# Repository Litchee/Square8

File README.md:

8 SQUARE - Heartbeat Necklace Soldering Kit
-------------

8 SQUARE is a lovely and eye catching necklace that shows off your geek attitude. We designed it to help you build up your confidence as a hardware maker. With the soldering iron held in your hand, and detailed tutorial aside, you can make a red heart bounce on the 8x8 LED matrix. 

**Easy to Solder**

8 SQUARE is friendly when it comes to soldering. Components chosen to fulfill the function are all easiest to solder and appropriate distance between each two pads is kept to ensure people without any soldering experience can get it run with only a little effort.

**Arduino Compatible Microcontroller**

8 SQUARE features a classic Atmega328 as its processor. You can totally reprogram it as a Arduino UNO - the most widely adapted Arduino board for now. Thousands of tutorials and libraries over the community are easily to found when you need help to support your next Arduino project with 8 SQUARE.

**Friendly to Sewing**

7 signal pins and 4 power pins are routed our as much larger circular pads along 8 SQUARE. They are designed for further exploration with fabric. The through hole of these signals are large enough to let you put through any regular needles and tie a knot to confirm the connection.  

<br>
**Part List**

- Base board x 1
- 1k ohm resistor x 4
- 2k ohm resistor x 1
- 10k ohm resistor x 1
- 100nF capacitor x 4
- 3mm red LED x 1
- 3mm green LED x 1
- Push button x 1
- Switch x 1
- Coin battery holder x 1
- LIR2032 coin battery x 1
- 8 pin female header x 2
- 8x8 LED matrix x 1
- leather rope x 1
- ring x 1
- tutorial x 1

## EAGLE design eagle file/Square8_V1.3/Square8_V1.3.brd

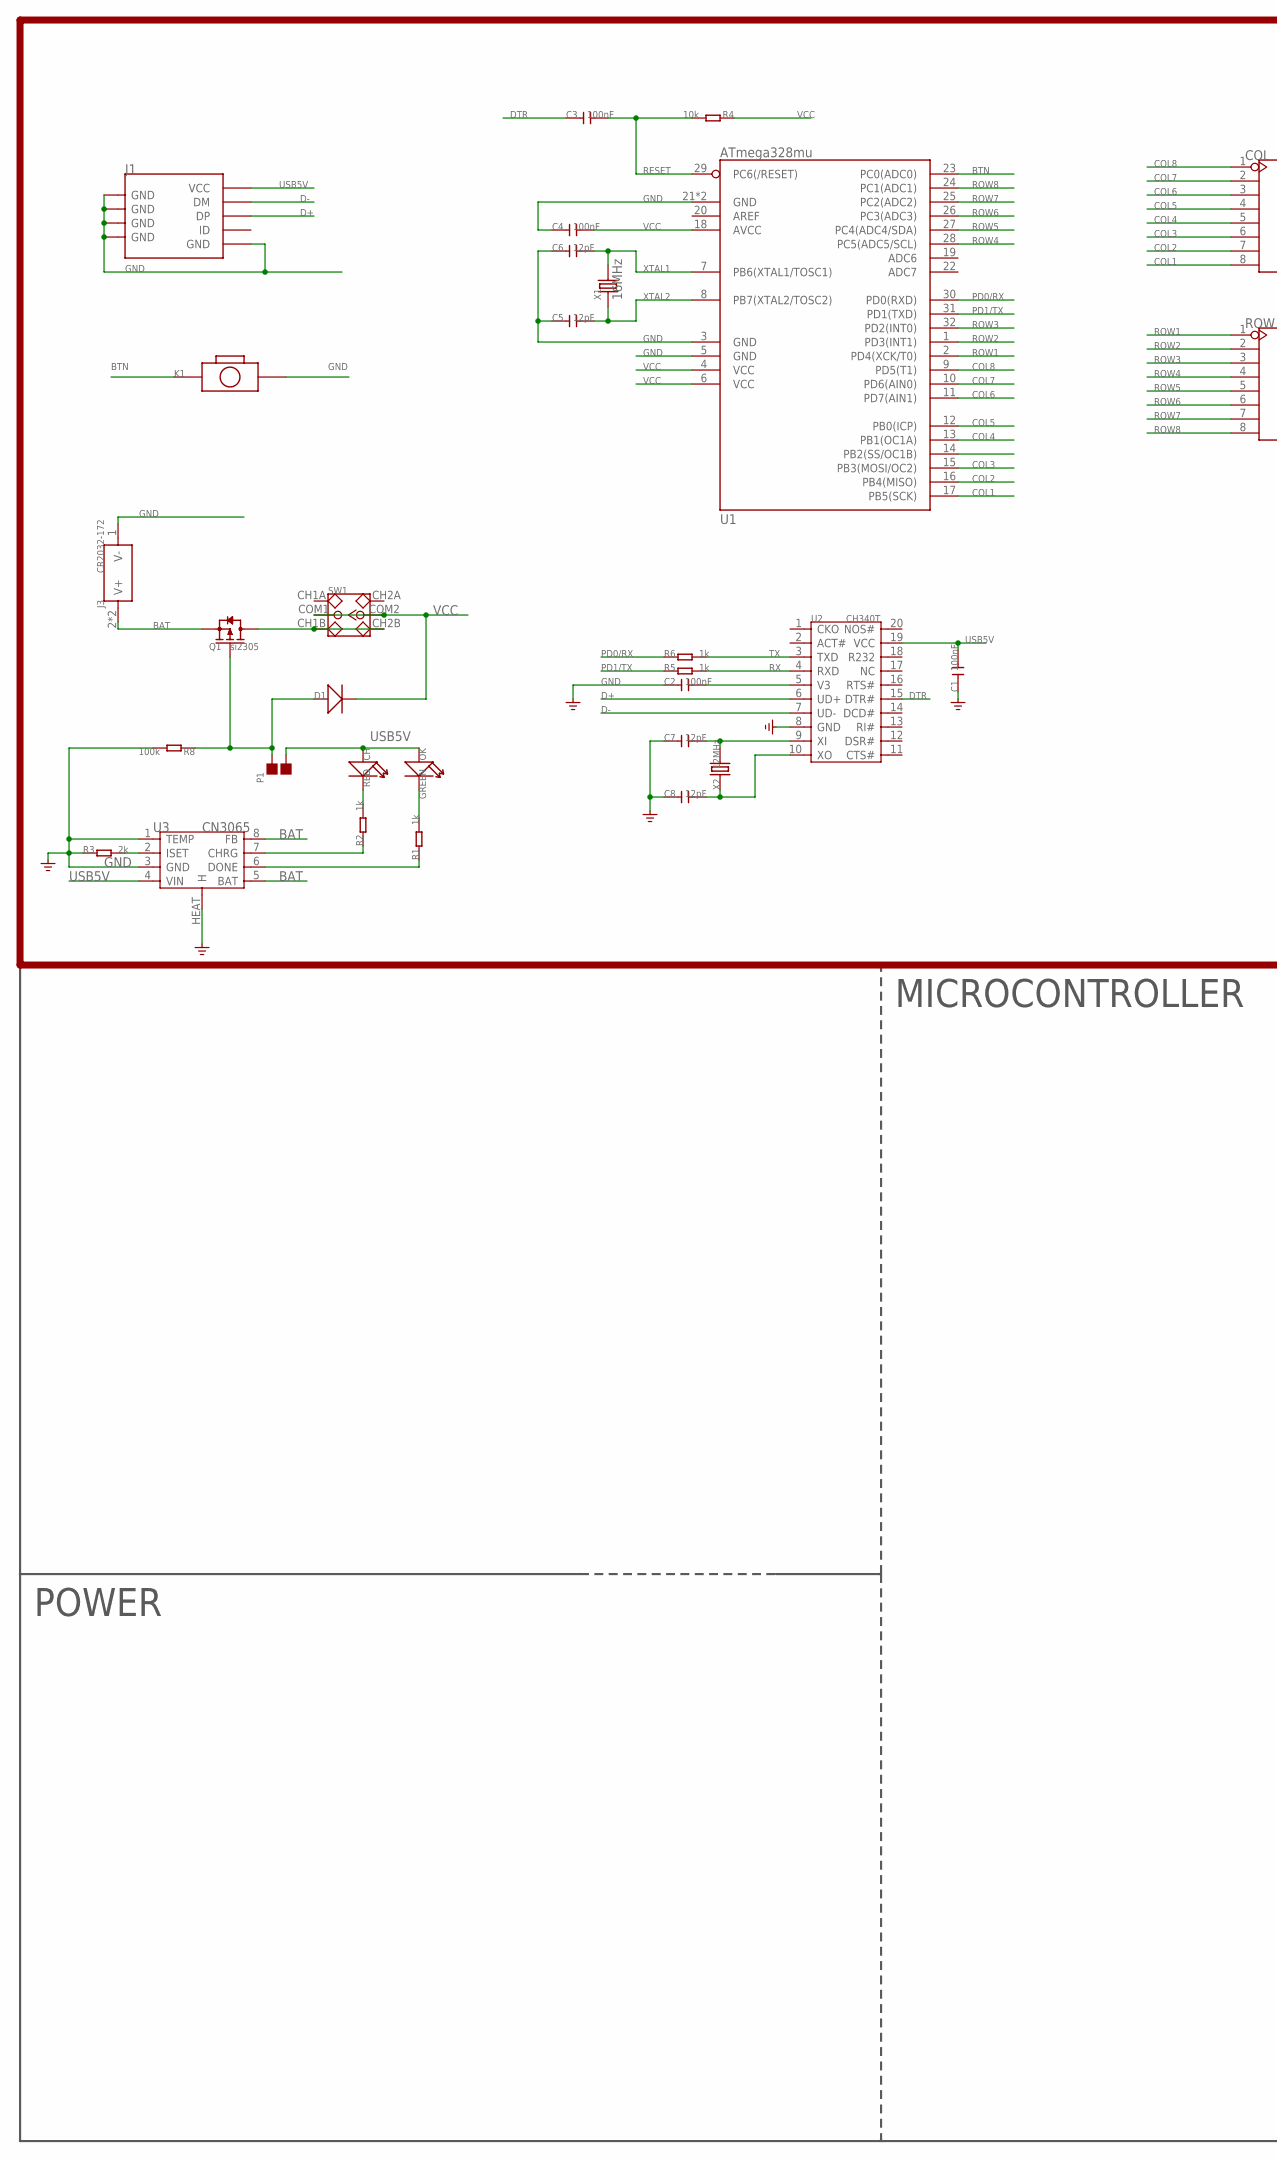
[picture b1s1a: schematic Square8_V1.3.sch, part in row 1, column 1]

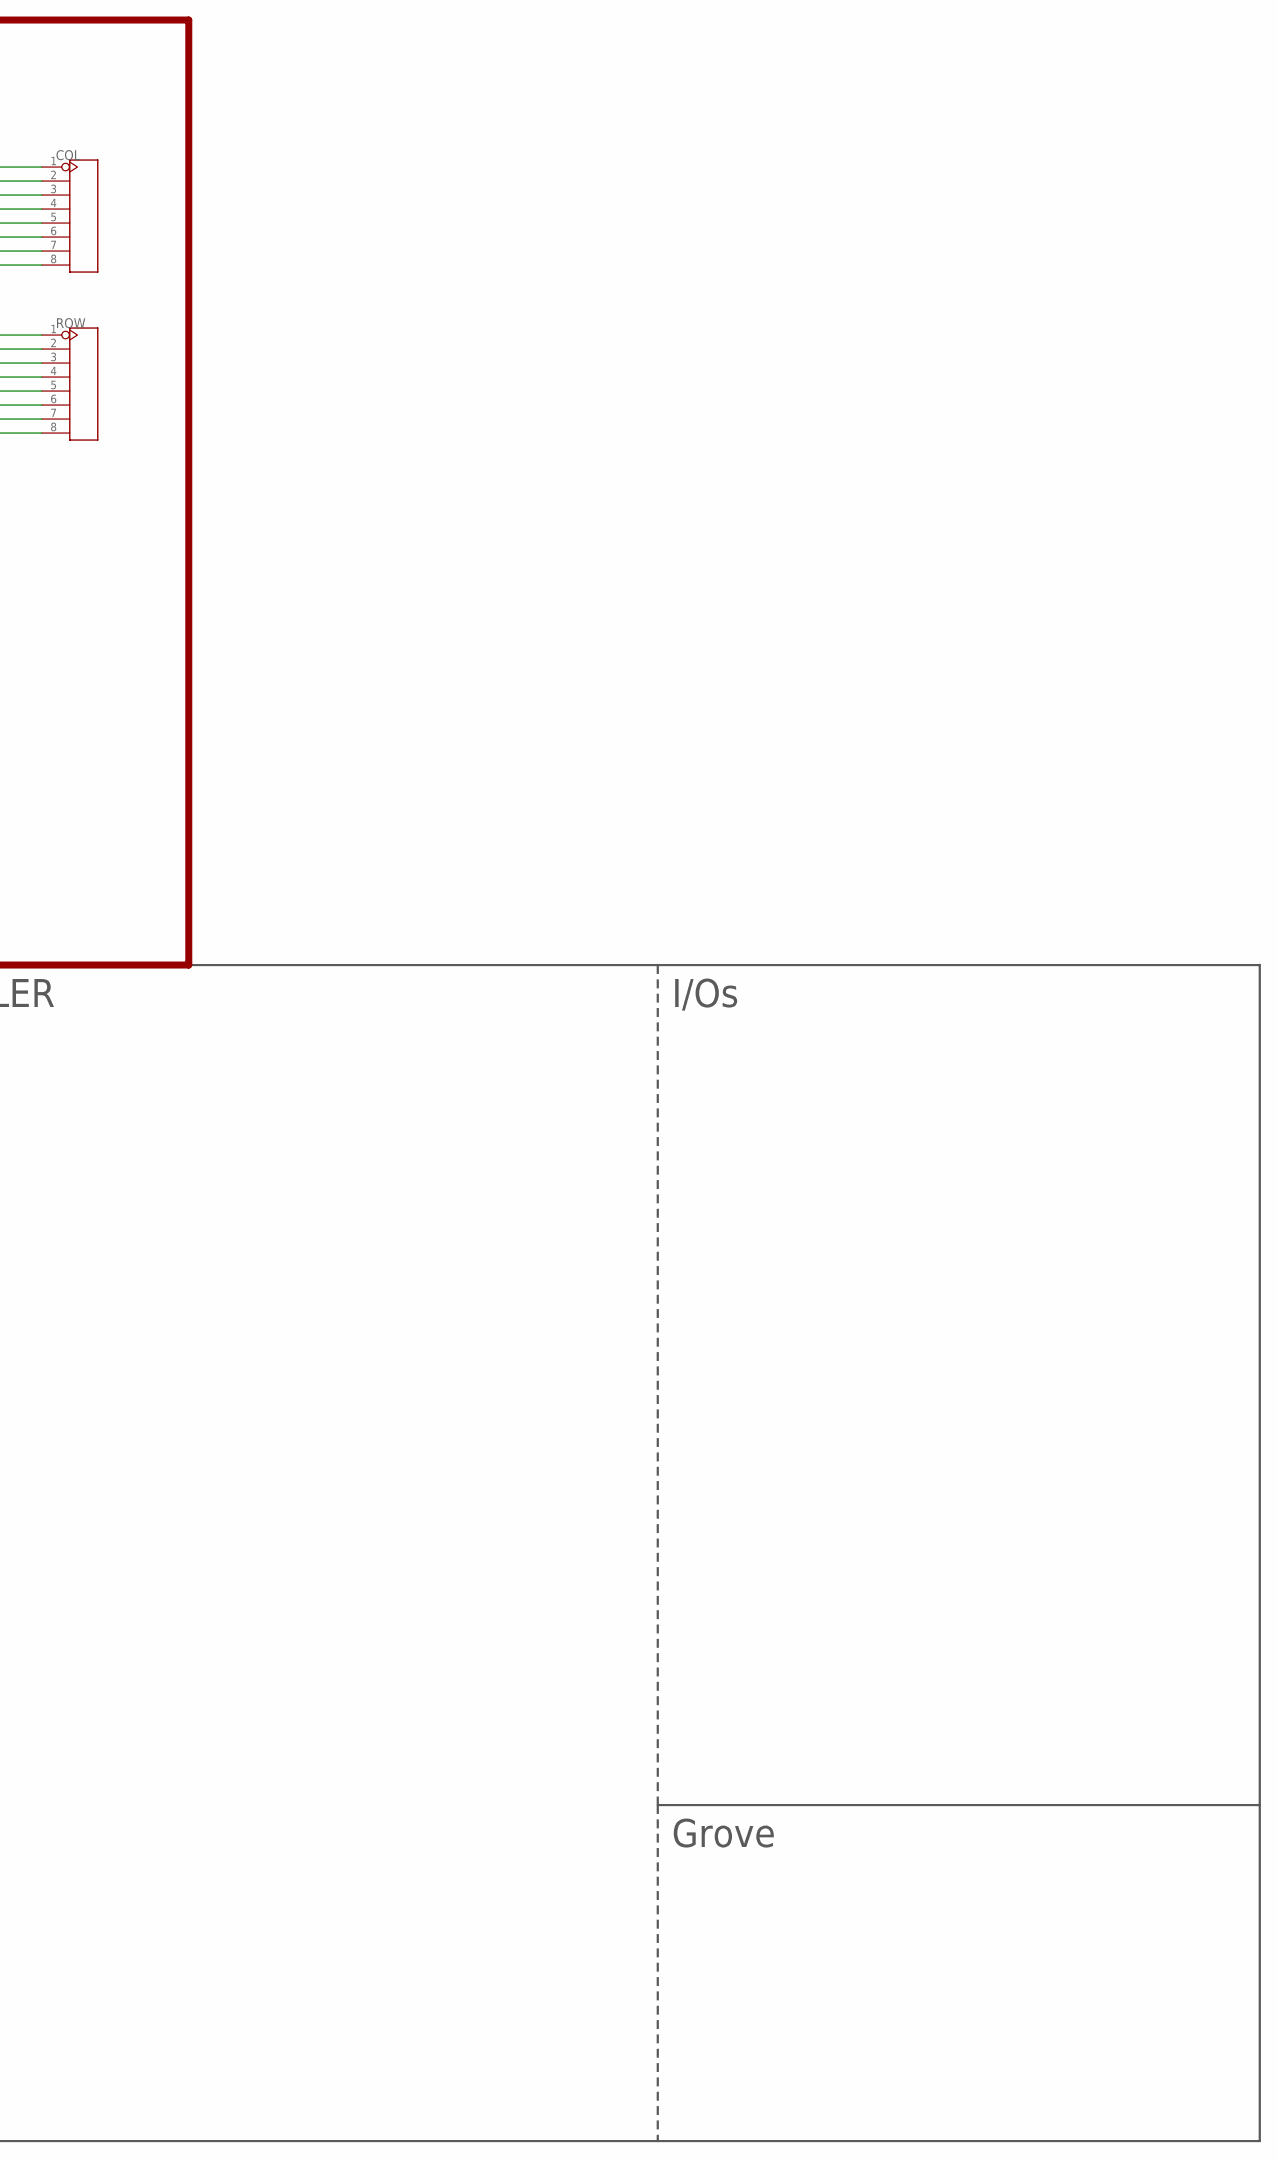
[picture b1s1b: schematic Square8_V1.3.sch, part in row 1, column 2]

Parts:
C1, C2, C3, C4: 100nF; CERAMIC-2.54
C5, C6, C7, C8: 12pF; C0603
CH: RED; LED-2P-2.54-3MM
COL: HEADER-8P-2.54; 8P-2.54
D1: D'B130L-13-F'; SMA
J1: USB-MINIUSB-5P-MICRO; MICRO-USB
J3: CR2032-172; 2032-D20-CIRCLE
K1: BUTTON-2P'TS-1101F'; 2P-3.4X6.0X3.55H-90D
OK: GREEN; LED-2P-2.54-3MM
P1: PAD-JUMPER-2P; 2P-SMD-1.78X1.27
Q1: si2305; SOT23
R1, R2, R5, R6: 1k; R0204/7
R3: 2k; R0204/7
R4: 10k; R0204/7
R8: 100k; R0603
ROW: HEADER-8P-2.54; 8P-2.54
SW1: SWITCH-2CH-6P'90D'; 6P-2CH-2.5-9.1X3.5X3.2H-90D
U1: ATmega328mu; MLF32X-W/HEAT
U2: CH340T; SSOP20
U3: CN3065; DFN8
X1: 16MHz; HC49S
X2: 12MHz; HC49S

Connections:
BAT: J3.2 (V+), J3.3 (V+), Q1.2 (S), U3.5 (BAT), U3.8 (FB)
BTN: K1.P$1 (1), U1.23 (PC0(ADC0))
CH_STATE: R1.1, U3.6 (DONE)
COL1: COL.8, U1.17 (PB5(SCK))
COL2: COL.7, U1.16 (PB4(MISO))
COL3: COL.6, U1.15 (PB3(MOSI/OC2))
COL4: COL.5, U1.13 (PB1(OC1A))
COL5: COL.4, U1.12 (PB0(ICP))
COL6: COL.3, U1.11 (PD7(AIN1))
COL7: COL.2, U1.10 (PD6(AIN0))
COL8: COL.1, U1.9 (PD5(T1))
D+: J1.3 (DP), U2.6 (UD+)
D-: J1.2 (DM), U2.7 (UD-)
DTR: C3.1, U2.15 (DTR#)
GND: C1.1, C2.1, C4.1, C5.1, C6.1, C7.1, C8.1, J1.5 (GND), J1.S1 (GND), J1.S2 (GND), J1.S3 (GND), J1.S4 (GND), J1.S5 (GND), J1.S6 (GND), J3.1 (V-), K1.P$2 (2), R3.1, R8.2, U1.3 (GND), U1.5 (GND), U1.21 (GND), U1.HEAT (GND), U2.8 (GND), U3.1 (TEMP), U3.3 (GND), U3.HEAT (H)
unnamed: R2.1, U3.7 (CHRG)
unnamed: OK.K (-), R1.2
unnamed: D1.2 (+), P1.2, Q1.1 (G), R8.1
unnamed: CH.K (-), R2.2
unnamed: R3.2, U3.2 (ISET)
unnamed: C7.2, U2.9 (XI), X2.2
unnamed: C8.2, U2.10 (XO), X2.1
unnamed: Q1.3 (D), SW1.CH1B, SW1.CH2B
PD0/RX: R6.1, U1.30 (PD0(RXD))
PD1/TX: R5.1, U1.31 (PD1(TXD))
RESET: C3.2, R4.2, U1.29 (PC6(/RESET))
ROW1: ROW.1, U1.2 (PD4(XCK/T0))
ROW2: ROW.2, U1.1 (PD3(INT1))
ROW3: ROW.3, U1.32 (PD2(INT0))
ROW4: ROW.4, U1.28 (PC5(ADC5/SCL))
ROW5: ROW.5, U1.27 (PC4(ADC4/SDA))
ROW6: ROW.6, U1.26 (PC3(ADC3))
ROW7: ROW.7, U1.25 (PC2(ADC2))
ROW8: ROW.8, U1.24 (PC1(ADC1))
RX: R5.2, U2.4 (RXD)
TX: R6.2, U2.3 (TXD)
USB5V: C1.2, CH.A (+), J1.1 (VCC), OK.A (+), P1.1, U2.19 (VCC), U3.4 (VIN)
V3: C2.2, U2.5 (V3)
VCC: C4.2, D1.1 (-), R4.1, SW1.COM1, SW1.COM2, U1.4 (VCC), U1.6 (VCC), U1.18 (AVCC)
XTAL1: C6.2, U1.7 (PB6(XTAL1/TOSC1)), X1.2
XTAL2: C5.2, U1.8 (PB7(XTAL2/TOSC2)), X1.1

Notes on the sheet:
POWER
MICROCONTROLLER
I/Os
Grove

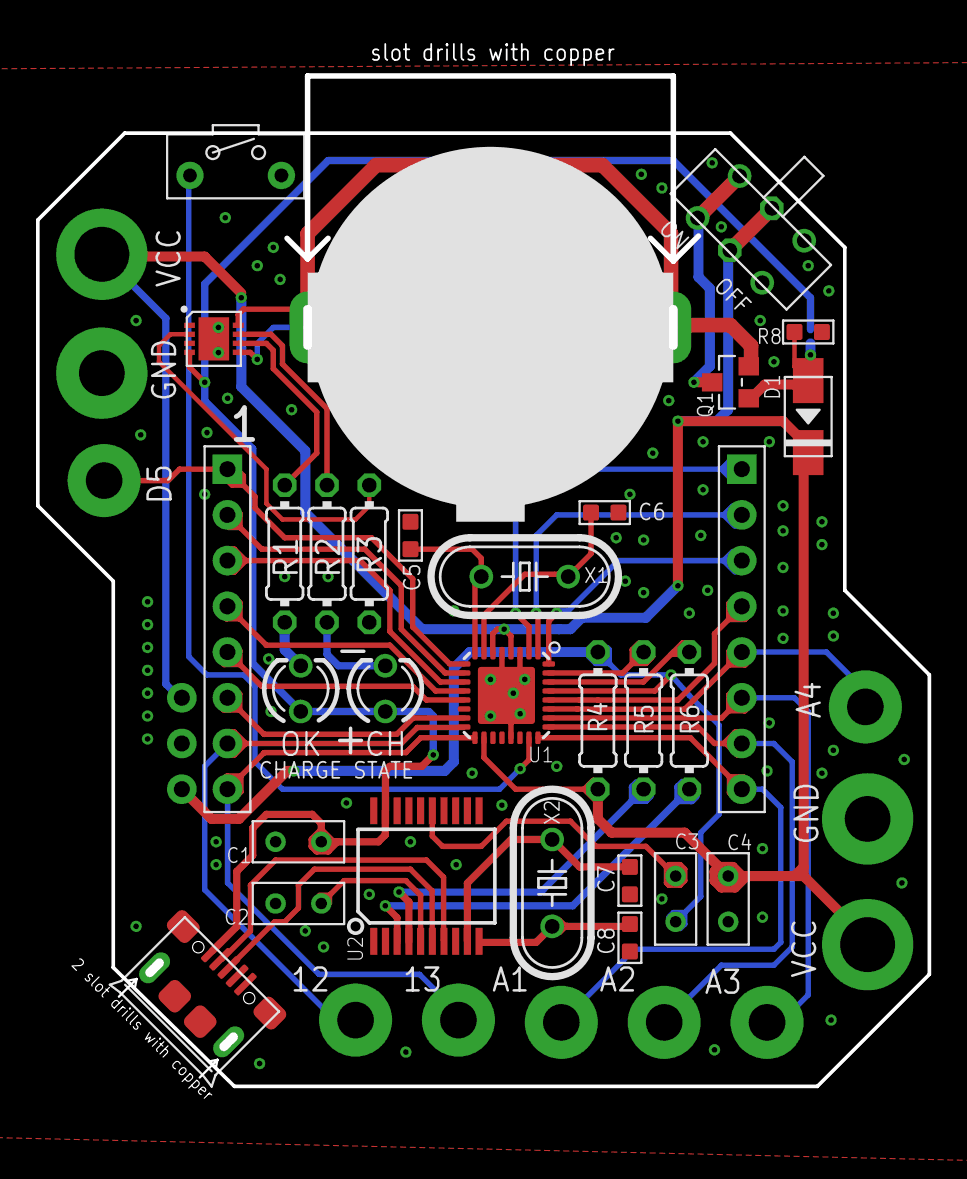
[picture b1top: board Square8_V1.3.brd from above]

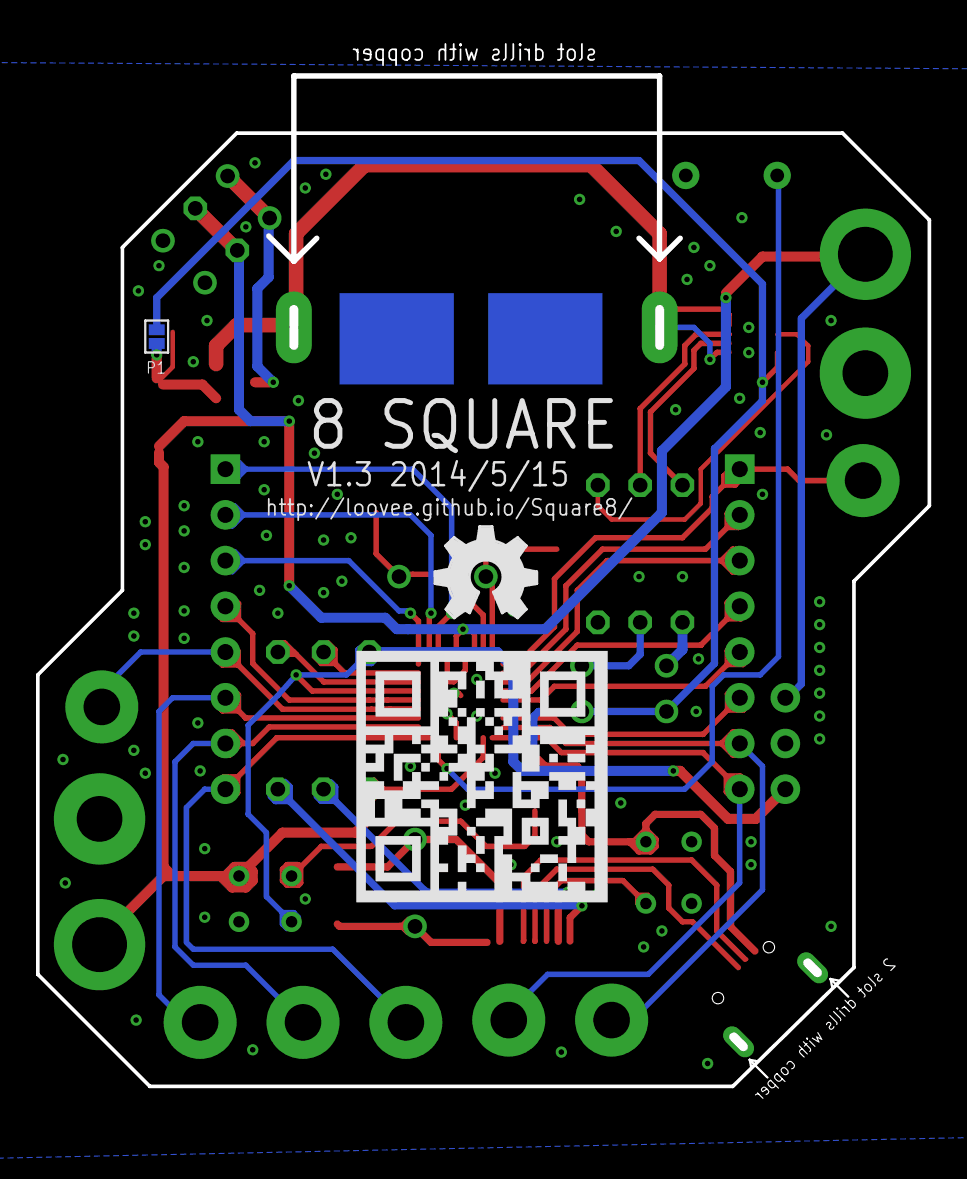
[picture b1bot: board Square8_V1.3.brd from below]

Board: 2 copper layers, 49.2 x 61.0 mm, 32 parts (2 on the bottom side), 41 nets.

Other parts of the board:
U$1: OSHW_FILLX200_NOTEXT

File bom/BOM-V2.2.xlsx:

Bill of Material from mf.sch, 28 parts, as of 2014/3/22 8:14:23
Part | Value | Package | Description | 用量 | Status | Lead Time | Qty | 预计目前余料 | 实际余料 | Unit Price
CH | RED | LED-2P-2.54-3MM 插件 |  | 1 |  |  | 1000 | 900 |  | 2.1999999999999999E-2 | 方舟电子
OK | GREEN | LED-2P-2.54-3MM 插件 |  | 1 |  |  | 1000 | 900 |  | 0.03
J3 | CR2032-172 | 2032-D20-CIRCLE 插件 | button cell holder | 1 |  |  | 110 | 10 |  | 0.15 | 天猫
LIR2032锂电池 |  |  |  | 1 |  |  | 110 | 10 |  | 2
C5,C6,C7,C8 | 12pF | C0603 贴片 | Ceramic Capacitors | 4 |  |  | 4000 | 3600 |  | 2.1999999999999999E-2 | 深中泰Q1A4282880078115
C1,C2,C3,C4 | 100nF | CERAMIC-2.54 插件 | Ceramic Capacitors | 4
R7 | 100k | R0603 贴片 |  | 1
R4 | 10k | R0204/7 插件 |  | 1 |  |  | 1000 | 900 |  | 6.4999999999999997E-3
R1,R2,R5,R6 | 1k | R0204/7 插件 |  | 4 |  |  | 1000 | 600 |  | 2.5999999999999999E-2
R3 | 2k | R0204/7 插件 |  | 1 |  |  | 1000 | 900 |  | 6.4999999999999997E-3
X1 | 16MHz | 2P-SMD-5X3.2 插件 | CRYSTAL | 1 |  |  | 200 | 100 |  | 0.23
X2 | 12MHz | 2P-SMD-5X3.2 插件 | CRYSTAL | 1 |  |  | 200 | 100 |  | 0.23
COL,ROL | HEADER-8P-2.54 | 8P-2.54 插件 | 排母 | 2 |  |  | 225 | 25 |  | 0.4 | 华强A373- 568318975
J1 | USB-MICRO-5P | MICRO-USB-5P 贴片 |  | 1 |  |  | 105 | 5 |  | 0.2
K1 |  | 2P-3.4X6.0X3.55H-90D 插件 |  | 1 |  |  | 1000 | 900 |  | 0.2
SW1 |  | 6P-2CH-2.5-9.1X3.5X3.2H-90D 插件 |  | 1 |  |  | 1000 | 900 |  | 0.08
8X8led点阵 |  | 插件 |  | 1 |  |  | 110 | 10 |  | 2.5 | 方舟电子
U1 | ATmega328mu | MLF32X-W/HEAT 贴片 | MICROCONTROLLER | 1 |  |  | 110 | 10 |  | 6.4 | 深圳市泽邦电子有限公司 | 艾秀丽 | 深圳市福田区华强北路赛格广场二楼2710柜 | 13724330241
U2 | CH340T | SSOP20 贴片 |  | 1 |  |  | 110 | 10 |  | 2.15 | 深圳市慧宇通科技有限公司
U3 | CN3065 | DFN8 贴片 |  | 1 |  |  | 110 | 10 |  | 2.35 | 深圳市慧宇通科技有限公司
佩戴用的绳子 |  |  |  | 1 |  |  | 120 | 20 |  | 0.25 | 天猫
环扣 |  |  |  | 1 |  |  | 3 | -97 |  | 0.01
固定夹 |  |  |  | 1 |  |  | 6 | -94 |  | 0.01
可焊接别针 |  | 15mm 贴片 |  | 1 |  |  | 110 | 10 |  | 0.01 | 佳佳五金店
PCB |  |  |  | 1 |  |  | 100 | 0 |  | 3.8
包装盒
Q1 | SI2305DS-T1-E3 | SOT-23 贴片 | P-Mosfet | 1

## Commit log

2014-04-09 push to git
2014-04-09 add hex file and eagle file
2014-04-09 add github url to eagle file
2014-04-16 add an two-dimension code to pcb
2014-04-17 update eagle file
2014-04-21 add a pmos, when usb inserted, power will on
2014-04-21 improve pcb
2014-04-28 add V1.2 eagle file
2014-04-28 add bom
2014-05-14 update eagle file to 1.3, inprove the layout, expecially the RST line
2014-06-20 test
2014-06-20 update read me
2014-07-04 dwin demo
2014-07-05 add some demo, improve the direction function, improve dispString
2014-07-06 v2.0
2014-07-07 add wdt to origin demo
